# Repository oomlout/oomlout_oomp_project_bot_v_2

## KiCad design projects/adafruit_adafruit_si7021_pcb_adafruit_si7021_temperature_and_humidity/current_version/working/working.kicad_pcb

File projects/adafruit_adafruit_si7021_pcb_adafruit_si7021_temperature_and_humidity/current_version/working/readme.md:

# adafruit_si7021_pcb
 
## summary 
* id: adafruit_adafruit_si7021_pcb_adafruit_si7021_temperature_and_humidity
* user: adafruit
* name: adafruit_si7021_pcb
* board: adafruit_si7021_temperature_and_humidity
* repo: https://github.com/adafruit/Adafruit-Si7021-PCB

* src_file_repo_sch: 
* src_file_repo_sch_link: https://github.com/adafruit/Adafruit-Si7021-PCB/tree/master/
* full details link: https://github.com/oomlout/oomlout_oomp_project_bot_v_2/tree/main/projects/adafruit_adafruit_si7021_pcb_adafruit_si7021_temperature_and_humidity/current_version/working  

## schematic  
  
[schematic (pdf)](working_schematic.pdf) 

## pcb  

[board (pdf)](working.pdf)  

## working_bom
| Id | Designator | Footprint | Quantity | Designation | Supplier and ref |  | None | 
| --- | --- | --- | --- | --- | --- | --- | --- | 
| 1 | Q1,Q2 | SOT23-WIDE | 2 | BSS138 |  |  | [''] | 
| 2 | R2,R3,R1,R4 | 0805-NO | 4 | 10K |  |  | [''] | 
| 3 | U$7,U$6 | MOUNTINGHOLE_2.5_PLATED | 2 | MOUNTINGHOLE2.5 |  |  | [''] | 
| 4 | C2,C3 | 0805-NO | 2 | 10uF |  |  | [''] | 
| 5 | JP1 | 1X05_ROUND_70 | 1 |  |  |  | [''] | 
| 6 | FID1,FID2 | FIDUCIAL_1MM | 2 | FIDUCIAL" |  |  | [''] | 
| 7 | U$1 | ADAFRUIT_2.5MM | 1 |  |  |  | [''] | 
| 8 | C1 | 0805-NO | 1 | 0.1uF |  |  | [''] | 
| 9 | U2 | DFN6_3X3_SI | 1 | Si7021-A20 |  |  | [''] | 
| 10 | U1 | SOT23-5 | 1 | MIC5225-3.3 |  |  | [''] | 
| 11 | U$10 | ADAFRUIT_3.5MM | 1 |  |  |  | [''] | 
| 12 | U$9 | PCBFEAT-REV-040 | 1 |  |  |  | [''] | 

## bom_schematic
| Ref | Qnty | Value | Cmp name | Footprint | Description | Vendor | DNP | 
| --- | --- | --- | --- | --- | --- | --- | --- | 
| C1 | 1 | 0.1uF | CAP_CERAMIC0805-NOOUTLINE | working:0805-NO |  |  |  | 
| C2, C3 | 2 | 10uF | CAP_CERAMIC0805-NOOUTLINE | working:0805-NO |  |  |  | 
| FID1, FID2 | 2 | FIDUCIAL"" | FIDUCIAL{dblquote}{dblquote} | working:FIDUCIAL_1MM |  |  |  | 
| JP1 | 1 | HEADER-1X570MIL | HEADER-1X570MIL | working:1X05_ROUND_70 |  |  |  | 
| Q1, Q2 | 2 | BSS138 | MOSFET-NWIDE | working:SOT23-WIDE |  |  |  | 
| R1, R2, R3, R4 | 4 | 10K | RESISTOR0805_NOOUTLINE | working:0805-NO |  |  |  | 
| U1 | 1 | MIC5225-3.3 | VREG_SOT23-5 | working:SOT23-5 |  |  |  | 
| U2 | 1 | Si7021-A20 | SI7021-A20 | working:DFN6_3X3_SI |  |  |  | 
| U$6, U$7 | 2 | MOUNTINGHOLE2.5 | MOUNTINGHOLE2.5 | working:MOUNTINGHOLE_2.5_PLATED |  |  |  | 

## mounting_holes
| x | y | package | value | ref | size | 
| --- | --- | --- | --- | --- | --- | 
| 10.16 | 0.0 | MOUNTINGHOLE_2.5_PLATED | MOUNTINGHOLE2.5 | U$6 | m3 | 
| 0.0 | 0.0 | MOUNTINGHOLE_2.5_PLATED | MOUNTINGHOLE2.5 | U$7 | m3 |

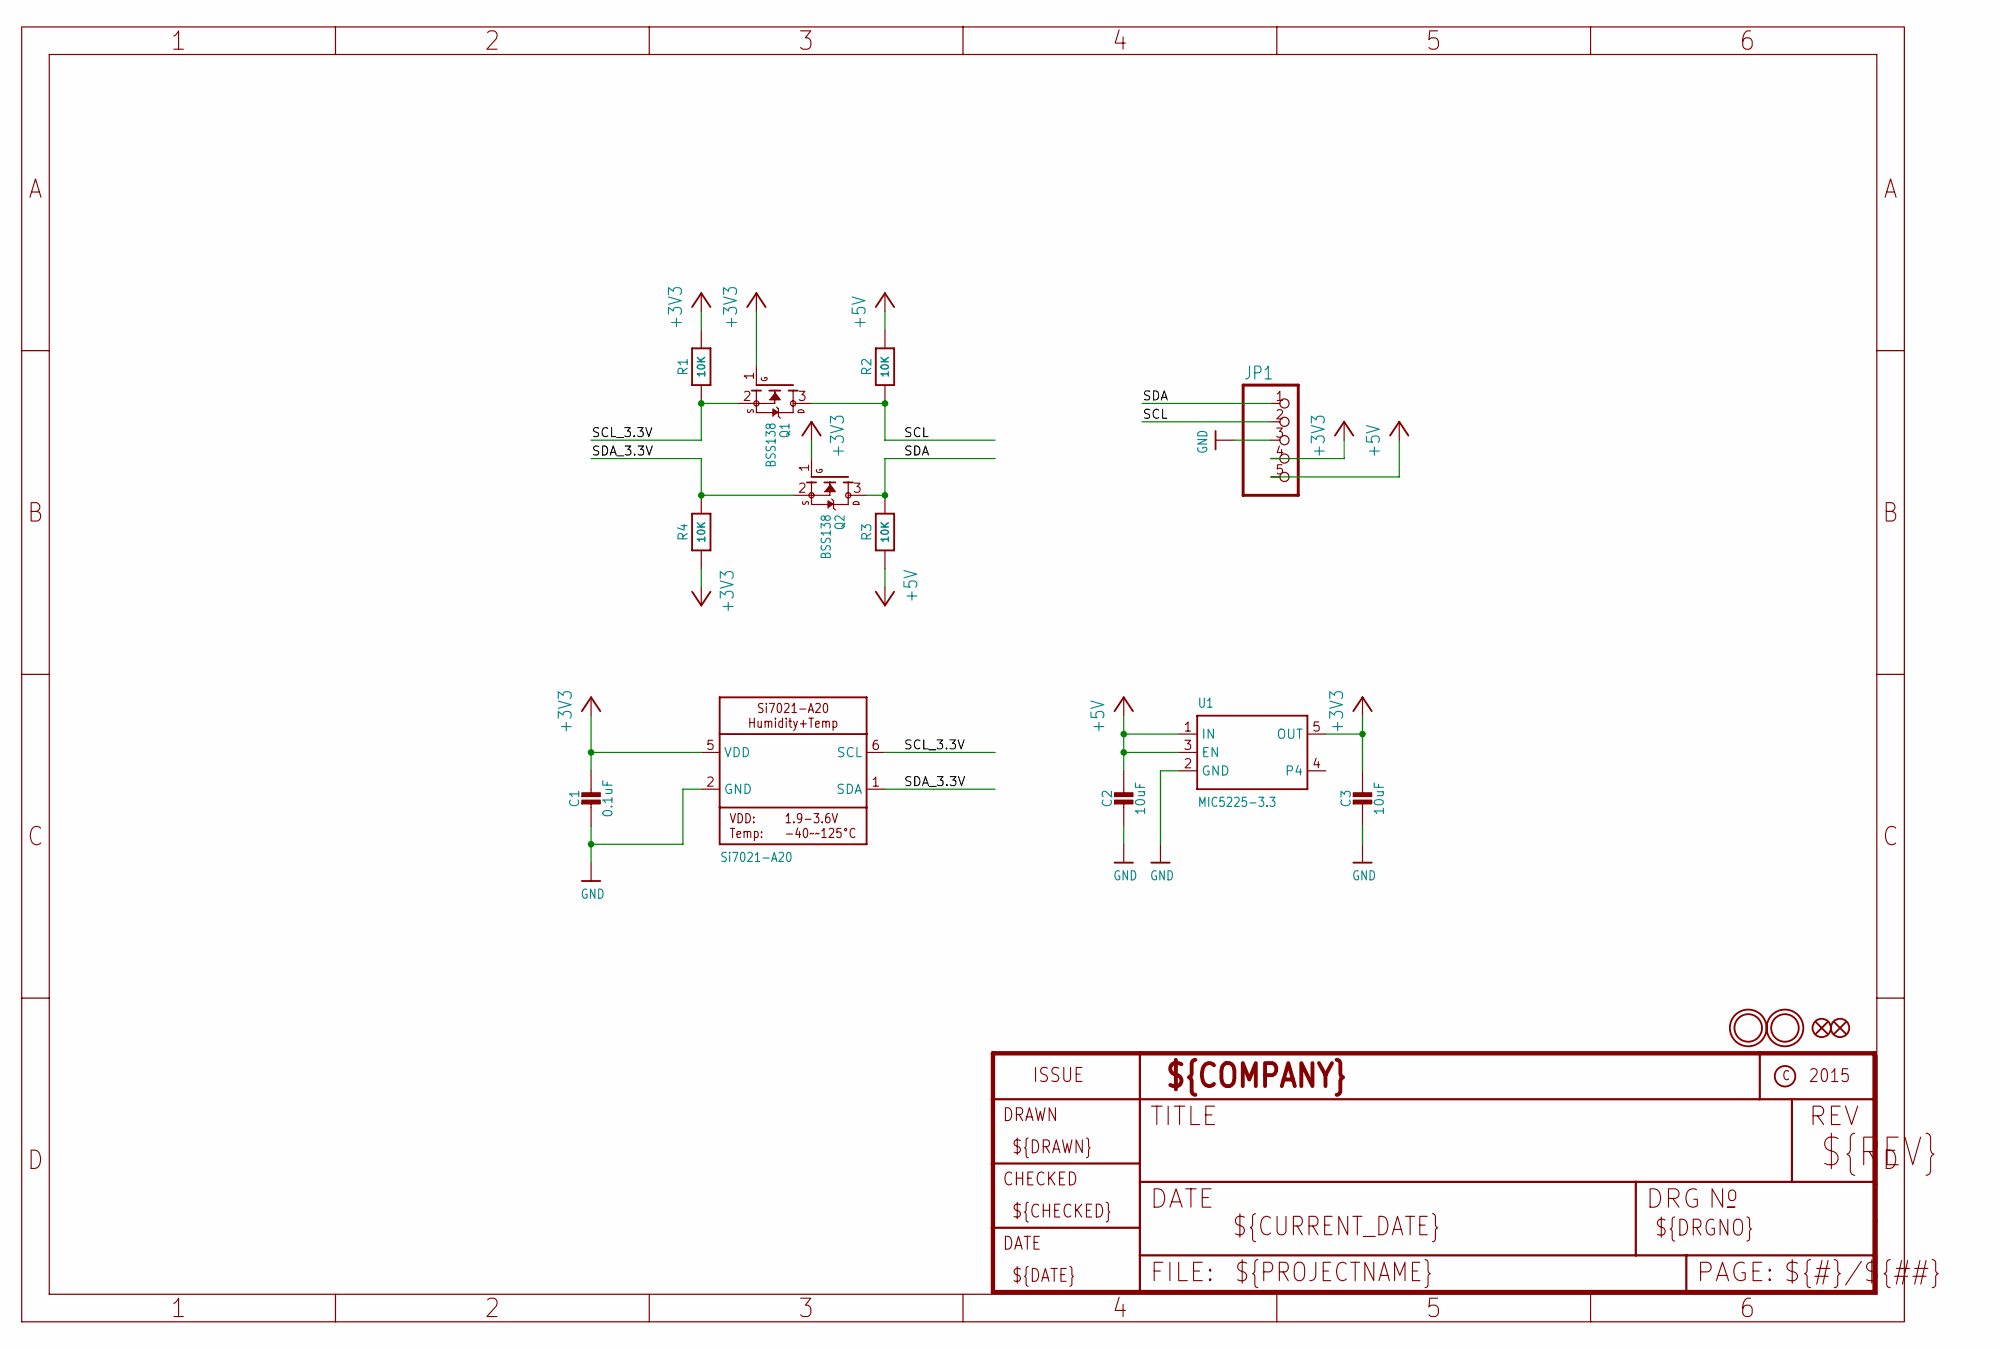
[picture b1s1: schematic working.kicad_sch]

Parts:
C1: 0.1uF; 0805-NO
C2, C3: 10uF; 0805-NO
FID1, FID2: FIDUCIAL""; FIDUCIAL_1MM
JP1: HEADER-1X570MIL; 1X05_ROUND_70
Q1, Q2: BSS138; SOT23-WIDE
R1, R2, R3, R4: 10K; 0805-NO
U1: MIC5225-3.3; SOT23-5
U2: Si7021-A20; DFN6_3X3_SI
U$6, U$7: MOUNTINGHOLE2.5; MOUNTINGHOLE_2.5_PLATED

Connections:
+3V3: C1.1, C3.1, JP1.4, Q1.1 (G), Q2.1 (G), R1.2, R4.1, U1.5 (OUT), U2.5 (VDD)
GND: C1.2, C2.2, C3.2, JP1.3, U1.2 (GND), U2.2 (GND)
SCL: JP1.2, Q1.3 (D), R2.1
SCL_3.3V: Q1.2 (S), R1.1, U2.6 (SCL)
SDA: JP1.1, Q2.3 (D), R3.2
SDA_3.3V: Q2.2 (S), R4.2, U2.1 (SDA)
VIN: C2.1, JP1.5, R2.2, R3.1, U1.1 (IN), U1.3 (EN)

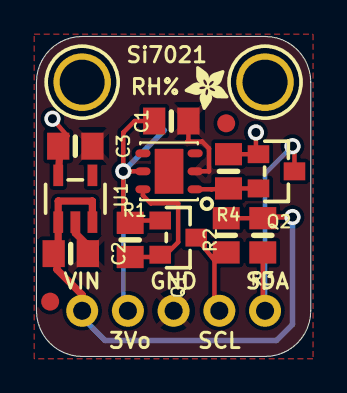
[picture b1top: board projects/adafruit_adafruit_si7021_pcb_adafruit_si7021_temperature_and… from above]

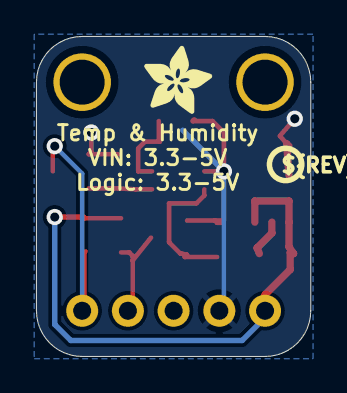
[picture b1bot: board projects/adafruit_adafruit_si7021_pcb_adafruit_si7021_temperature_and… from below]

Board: 2 copper layers, 15.2 x 17.8 mm, 19 parts (2 on the bottom side), 7 nets.

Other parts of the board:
U$1: ADAFRUIT_2.5MM
U$9: PCBFEAT-REV-040
U$10: ADAFRUIT_3.5MM

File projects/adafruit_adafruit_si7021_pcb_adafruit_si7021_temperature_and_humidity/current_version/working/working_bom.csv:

"Id";"Designator";"Footprint";"Quantity";"Designation";"Supplier and ref";
1;"Q1,Q2";"SOT23-WIDE";2;"BSS138";;;
2;"R2,R3,R1,R4";"0805-NO";4;"10K";;;
3;"U$7,U$6";"MOUNTINGHOLE_2.5_PLATED";2;"MOUNTINGHOLE2.5";;;
4;"C2,C3";"0805-NO";2;"10uF";;;
5;"JP1";"1X05_ROUND_70";1;"";;;
6;"FID1,FID2";"FIDUCIAL_1MM";2;"FIDUCIAL""";;;
7;"U$1";"ADAFRUIT_2.5MM";1;"";;;
8;"C1";"0805-NO";1;"0.1uF";;;
9;"U2";"DFN6_3X3_SI";1;"Si7021-A20";;;
10;"U1";"SOT23-5";1;"MIC5225-3.3";;;
11;"U$10";"ADAFRUIT_3.5MM";1;"";;;
12;"U$9";"PCBFEAT-REV-040";1;"";;;

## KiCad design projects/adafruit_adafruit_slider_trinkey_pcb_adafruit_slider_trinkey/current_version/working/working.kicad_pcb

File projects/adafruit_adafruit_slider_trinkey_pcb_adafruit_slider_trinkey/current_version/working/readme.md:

# adafruit_slider_trinkey_pcb
 
## summary 
* id: adafruit_adafruit_slider_trinkey_pcb_adafruit_slider_trinkey
* user: adafruit
* name: adafruit_slider_trinkey_pcb
* board: adafruit_slider_trinkey
* repo: https://github.com/adafruit/Adafruit-Slider-Trinkey-PCB

* src_file_repo_sch: 
* src_file_repo_sch_link: https://github.com/adafruit/Adafruit-Slider-Trinkey-PCB/tree/main/
* full details link: https://github.com/oomlout/oomlout_oomp_project_bot_v_2/tree/main/projects/adafruit_adafruit_slider_trinkey_pcb_adafruit_slider_trinkey/current_version/working  

## schematic  
  
[schematic (pdf)](working_schematic.pdf) 

## pcb  

[board (pdf)](working.pdf)  

## working_bom
| Id | Designator | Footprint | Quantity | Designation | Supplier and ref |  | None | 
| --- | --- | --- | --- | --- | --- | --- | --- | 
| 1 | LED2,LED1 | NEO3535_REVERSE | 2 | WS2812B_SK6812E |  |  | [''] | 
| 2 | POT1 | SLIDE_POT_35MM | 1 | SLIDE_POT_35MM |  |  | [''] | 
| 3 | CN1 | USBA_PCB | 1 | USB A |  |  | [''] | 
| 4 | TOUCH0 | TESTPOINT_ROUND_0.5MM | 1 |  |  |  | [''] | 
| 5 | C3,C8 | 0805-NO | 2 | 10uF |  |  | [''] | 
| 6 | RST0,SWD0 | TP16R | 2 | TPTP16R |  |  | [''] | 
| 7 | U1 | SOT23-5 | 1 | AP2112K-3.3 |  |  | [''] | 
| 8 | FID2,FID1 | FIDUCIAL_1MM | 2 | FIDUCIAL_1MM |  |  | [''] | 
| 9 | C4,C5 | 0603-NO | 2 | 1uF |  |  | [''] | 
| 10 | SWC0 | TP15R | 1 | TPTP15R |  |  | [''] | 
| 11 | IC3 | QFN32_5MM | 1 | ATSAMD21E |  |  | [''] | 
| 12 | U$6 | ADAFRUIT_9MM | 1 |  |  |  | [''] | 
| 13 | U$8 | PCBFEAT-REV-040 | 1 |  |  |  | [''] | 
| 14 | Q2 | BTN_KMR2_4.6X2.8 | 1 | reset |  |  | [''] | 

## bom_schematic
| Ref | Qnty | Value | Cmp name | Footprint | Description | Vendor | DNP | 
| --- | --- | --- | --- | --- | --- | --- | --- | 
| C3, C8 | 2 | 10uF | CAP_CERAMIC0805-NOOUTLINE | working:0805-NO |  |  |  | 
| C4, C5 | 2 | 1uF | CAP_CERAMIC0603_NO | working:0603-NO |  |  |  | 
| CN1 | 1 | USB A | USB_TYPEAPCB | working:USBA_PCB |  |  |  | 
| FID1, FID2 | 2 | FIDUCIAL_1MM | FIDUCIAL_1MM | working:FIDUCIAL_1MM |  |  |  | 
| IC3 | 1 | ATSAMD21E | ATSAMD21E | working:QFN32_5MM |  |  |  | 
| LED1, LED2 | 2 | WS2812B_SK6812E | WS2812B_SK6812E | working:NEO3535_REVERSE |  |  |  | 
| POT1 | 1 | SLIDE_POT_35MM | SLIDE_POT_35MM | working:SLIDE_POT_35MM |  |  |  | 
| Q2 | 1 | reset | SWITCH_TACT_SMT4.6X2.8 | working:BTN_KMR2_4.6X2.8 |  |  |  | 
| RST0 | 1 | TPTP16R | TPTP16R | working:TP16R |  |  |  | 
| SWC0 | 1 | TPTP15R | TPTP15R | working:TP15R |  |  |  | 
| SWD0 | 1 | TPTP16R | TPTP16R | working:TP16R |  |  |  | 
| TOUCH0 | 1 | TESTPOINTROUND0.5MM | TESTPOINTROUND0.5MM | working:TESTPOINT_ROUND_0.5MM |  |  |  | 
| U1 | 1 | AP2112K-3.3 | VREG_SOT23-5 | working:SOT23-5 |  |  |  |

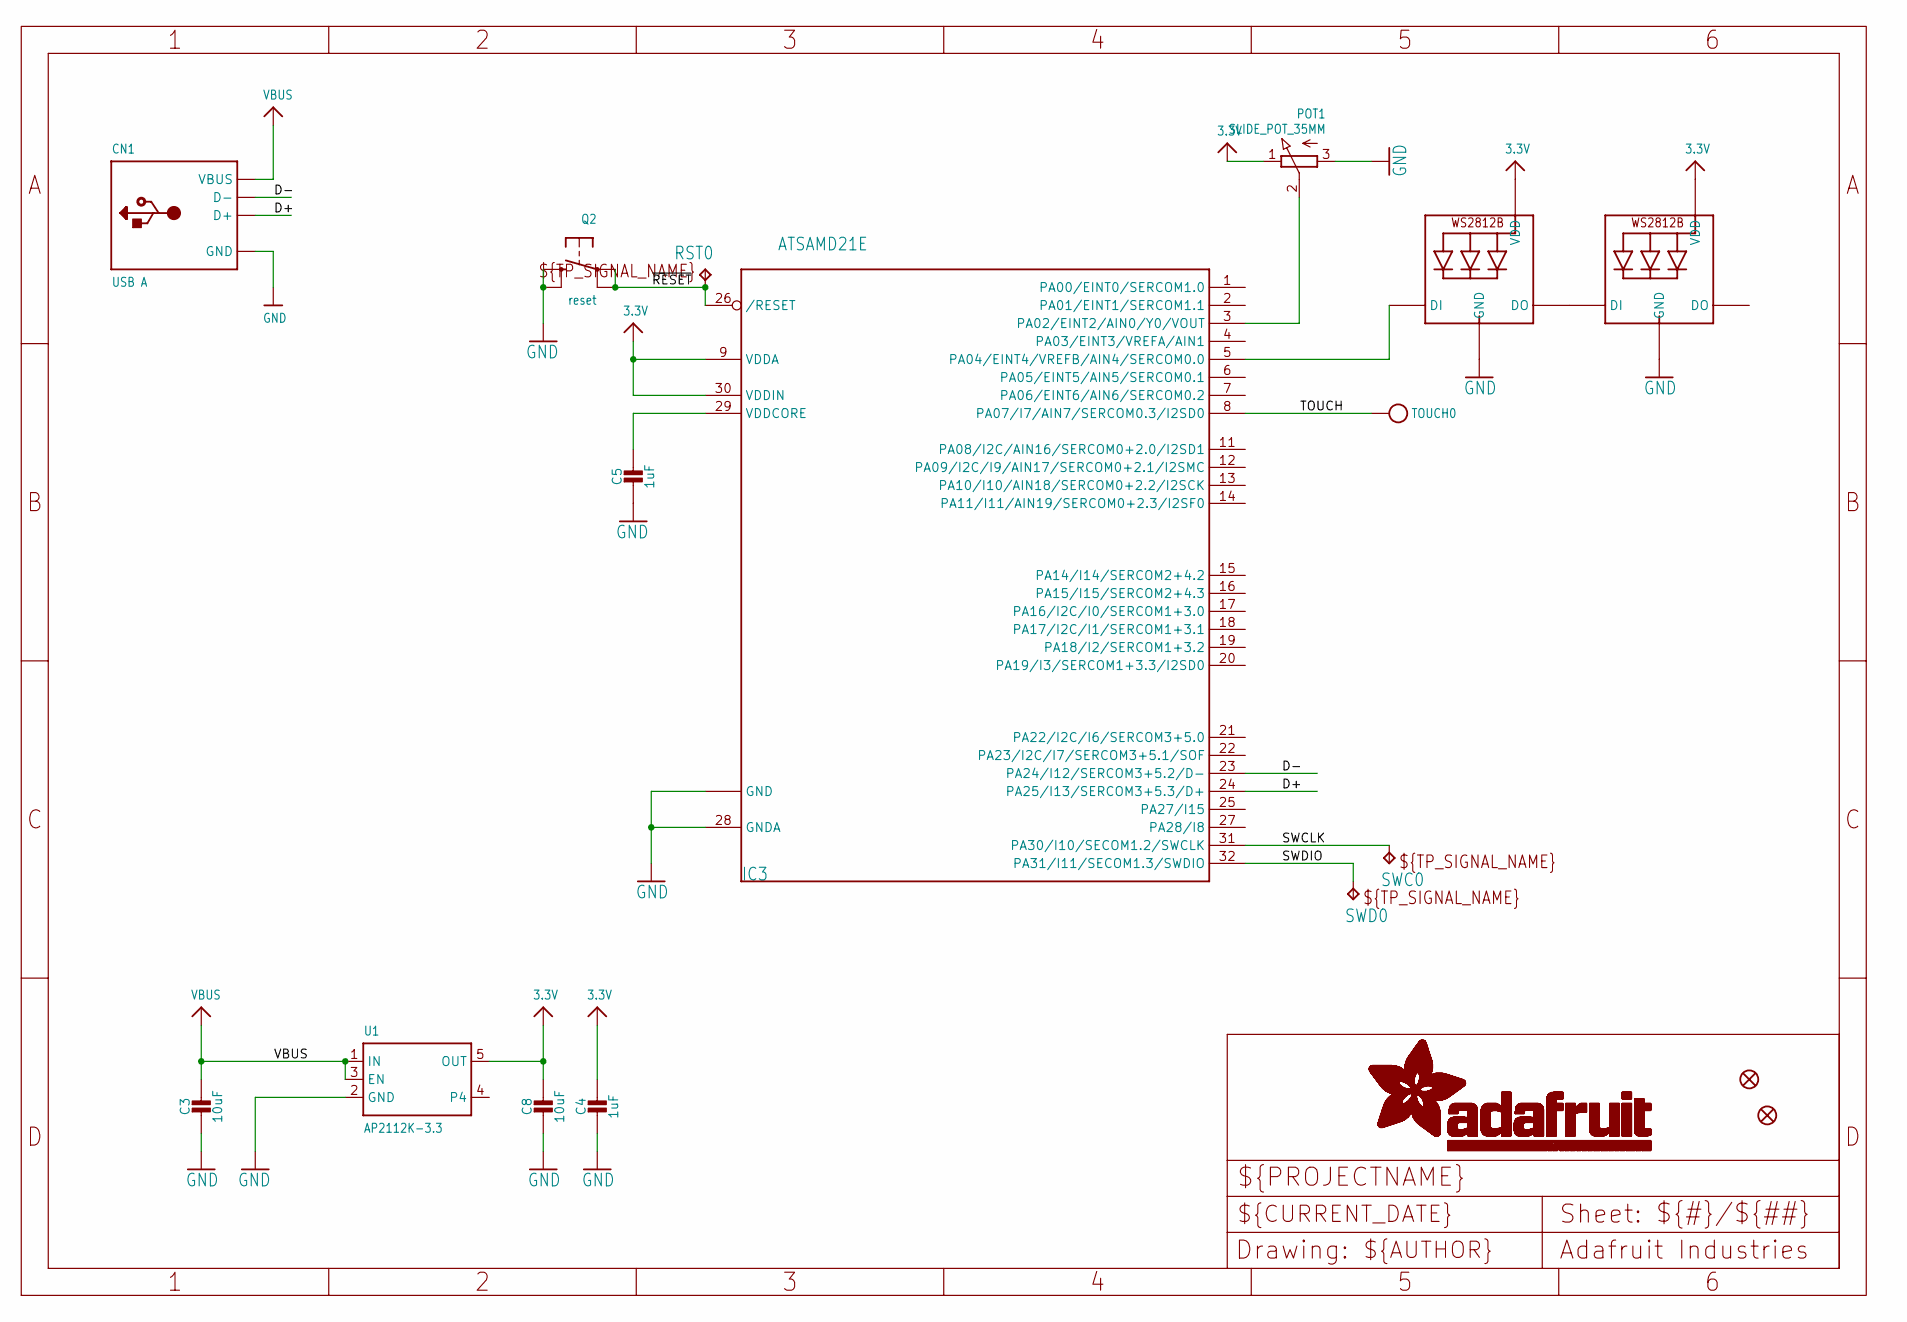
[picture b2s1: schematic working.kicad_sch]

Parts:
C3, C8: 10uF; 0805-NO
C4, C5: 1uF; 0603-NO
CN1: USB A; USBA_PCB
FID1, FID2: FIDUCIAL_1MM
IC3: ATSAMD21E; QFN32_5MM
LED1, LED2: WS2812B_SK6812E; NEO3535_REVERSE
POT1: SLIDE_POT_35MM
Q2: reset; BTN_KMR2_4.6X2.8
RST0: TPTP16R; TP16R
SWC0: TPTP15R; TP15R
SWD0: TPTP16R; TP16R
TOUCH0: TESTPOINTROUND0.5MM; TESTPOINT_ROUND_0.5MM
U1: AP2112K-3.3; SOT23-5

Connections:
3.3V: C4.1, C8.1, IC3.9 (VDDA), IC3.30 (VDDIN), LED1.1-VDD (VDD), LED2.1-VDD (VDD), POT1.1 (E), U1.5 (OUT)
D+: CN1.USB_PLUS (D+), IC3.24 (PA25/I13/SERCOM3+5.3/D+)
D-: CN1.USB_NEG (D-), IC3.23 (PA24/I12/SERCOM3+5.2/D-)
GND: C3.2, C4.2, C5.2, C8.2, CN1.GND, IC3.10 (GND), IC3.28 (GNDA), IC3.33 (GND), LED1.3-GND (GND), LED2.3-GND (GND), POT1.3 (A), Q2.B (S), Q2.B' (S1), U1.2 (GND)
unnamed: IC3.5 (PA04/EINT4/VREFB/AIN4/SERCOM0.0), LED1.4-DIN (DI)
unnamed: LED1.2-DOUT (DO), LED2.4-DIN (DI)
POT: IC3.3 (PA02/EINT2/AIN0/Y0/VOUT), POT1.2 (S)
SWCLK: IC3.31 (PA30/I10/SECOM1.2/SWCLK), SWC0.TP
SWDIO: IC3.32 (PA31/I11/SECOM1.3/SWDIO), SWD0.TP
TOUCH: IC3.8 (PA07/I7/AIN7/SERCOM0.3/I2SD0), TOUCH0.P$1
VBUS: C3.1, CN1.VCC (VBUS), U1.1 (IN), U1.3 (EN)
VDDCORE1: C5.1, IC3.29 (VDDCORE)
~RESET: IC3.26 (/RESET), Q2.A, Q2.A' (P1), RST0.TP

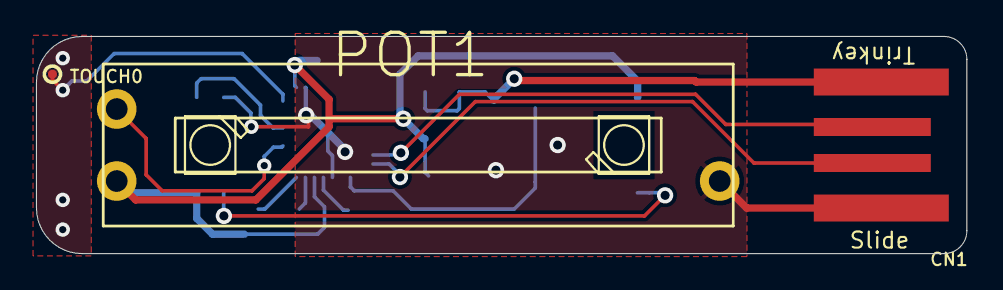
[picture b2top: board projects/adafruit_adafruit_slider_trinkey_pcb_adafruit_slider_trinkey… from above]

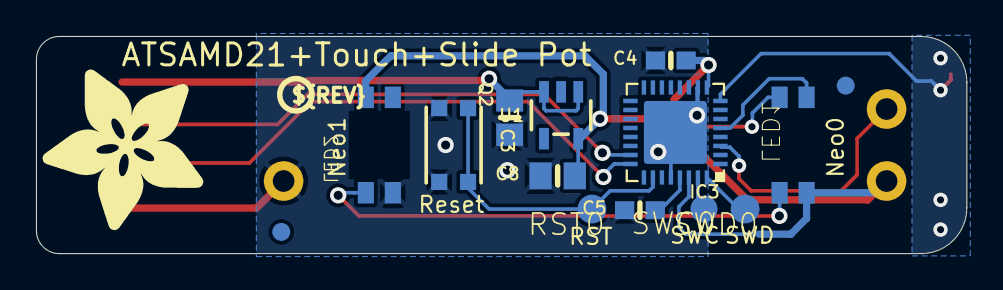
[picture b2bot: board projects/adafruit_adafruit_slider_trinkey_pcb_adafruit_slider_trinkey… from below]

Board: 2 copper layers, 51.7 x 12.1 mm, 19 parts (14 on the bottom side), 13 nets.

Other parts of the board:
U$6: ADAFRUIT_9MM
U$8: PCBFEAT-REV-040

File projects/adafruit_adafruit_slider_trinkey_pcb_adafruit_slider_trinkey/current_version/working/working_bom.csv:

"Id";"Designator";"Footprint";"Quantity";"Designation";"Supplier and ref";
1;"LED2,LED1";"NEO3535_REVERSE";2;"WS2812B_SK6812E";;;
2;"POT1";"SLIDE_POT_35MM";1;"SLIDE_POT_35MM";;;
3;"CN1";"USBA_PCB";1;"USB A";;;
4;"TOUCH0";"TESTPOINT_ROUND_0.5MM";1;"";;;
5;"C3,C8";"0805-NO";2;"10uF";;;
6;"RST0,SWD0";"TP16R";2;"TPTP16R";;;
7;"U1";"SOT23-5";1;"AP2112K-3.3";;;
8;"FID2,FID1";"FIDUCIAL_1MM";2;"FIDUCIAL_1MM";;;
9;"C4,C5";"0603-NO";2;"1uF";;;
10;"SWC0";"TP15R";1;"TPTP15R";;;
11;"IC3";"QFN32_5MM";1;"ATSAMD21E";;;
12;"U$6";"ADAFRUIT_9MM";1;"";;;
13;"U$8";"PCBFEAT-REV-040";1;"";;;
14;"Q2";"BTN_KMR2_4.6X2.8";1;"reset";;;

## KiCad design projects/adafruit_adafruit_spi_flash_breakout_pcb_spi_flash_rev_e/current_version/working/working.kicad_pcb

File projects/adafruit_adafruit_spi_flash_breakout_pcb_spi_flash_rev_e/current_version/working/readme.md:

# adafruit_spi_flash_breakout_pcb
 
## summary 
* id: adafruit_adafruit_spi_flash_breakout_pcb_spi_flash_rev_e
* user: adafruit
* name: adafruit_spi_flash_breakout_pcb
* board: spi_flash_rev_e
* repo: https://github.com/adafruit/Adafruit-SPI-Flash-Breakout-PCB

* src_file_repo_sch: 
* src_file_repo_sch_link: https://github.com/adafruit/Adafruit-SPI-Flash-Breakout-PCB/tree/main/
* full details link: https://github.com/oomlout/oomlout_oomp_project_bot_v_2/tree/main/projects/adafruit_adafruit_spi_flash_breakout_pcb_spi_flash_rev_e/current_version/working  

## schematic  
  
[schematic (pdf)](working_schematic.pdf) 

## pcb  

[board (pdf)](working.pdf)  

## working_bom
| Id | Designator | Footprint | Quantity | Designation | Supplier and ref |  | None | 
| --- | --- | --- | --- | --- | --- | --- | --- | 
| 1 | C3,C4 | 0805-NO | 2 | 10uF |  |  | [''] | 
| 2 | C1 | 0603-NO | 1 | 0.1uF |  |  | [''] | 
| 3 | R1 | 0603-NO | 1 | 10K |  |  | [''] | 
| 4 | U$13 | ADAFRUIT_2.5MM | 1 |  |  |  | [''] | 
| 5 | U1 | SOIC8_208MIL | 1 | Generic SPI Flash |  |  | [''] | 
| 6 | U4 | SOT23-5 | 1 | AP2127K-3.3 |  |  | [''] | 
| 7 | FID3,FID2 | FIDUCIAL_1MM | 2 | FIDUCIAL_1MM |  |  | [''] | 
| 8 | JP2 | 1X07_ROUND_70 | 1 |  |  |  | [''] | 
| 9 | U$16,U$17 | MOUNTINGHOLE_2.5_PLATED | 2 | MOUNTINGHOLE2.5 |  |  | [''] | 
| 10 | U3 | TSSOP16 | 1 | 74HC4050D |  |  | [''] | 
| 11 | U$21 | PCBFEAT-REV-040 | 1 |  |  |  | [''] | 

## bom_schematic
| Ref | Qnty | Value | Cmp name | Footprint | Description | Vendor | DNP | 
| --- | --- | --- | --- | --- | --- | --- | --- | 
| C1 | 1 | 0.1uF | CAP_CERAMIC0603_NO | working:0603-NO |  |  |  | 
| C3, C4 | 2 | 10uF | CAP_CERAMIC0805-NOOUTLINE | working:0805-NO |  |  |  | 
| FID2, FID3 | 2 | FIDUCIAL_1MM | FIDUCIAL_1MM | working:FIDUCIAL_1MM |  |  |  | 
| JP2 | 1 | HEADER-1X770MIL | HEADER-1X770MIL | working:1X07_ROUND_70 |  |  |  | 
| R1 | 1 | 10K | RESISTOR_0603_NOOUT | working:0603-NO |  |  |  | 
| U1 | 1 | Generic SPI Flash | SPIFLASH_8PIN208MIL | working:SOIC8_208MIL |  |  |  | 
| U3 | 1 | 74HC4050D | 74HC4050DTSSOP | working:TSSOP16 |  |  |  | 
| U4 | 1 | AP2127K-3.3 | VREG_SOT23-5 | working:SOT23-5 |  |  |  | 
| U$16, U$17 | 2 | MOUNTINGHOLE2.5 | MOUNTINGHOLE2.5 | working:MOUNTINGHOLE_2.5_PLATED |  |  |  | 

## mounting_holes
| x | y | package | value | ref | size | 
| --- | --- | --- | --- | --- | --- | 
| 0.0 | 0.0 | MOUNTINGHOLE_2.5_PLATED | MOUNTINGHOLE2.5 | U$16 | m3 | 
| 15.24 | 0.0 | MOUNTINGHOLE_2.5_PLATED | MOUNTINGHOLE2.5 | U$17 | m3 |

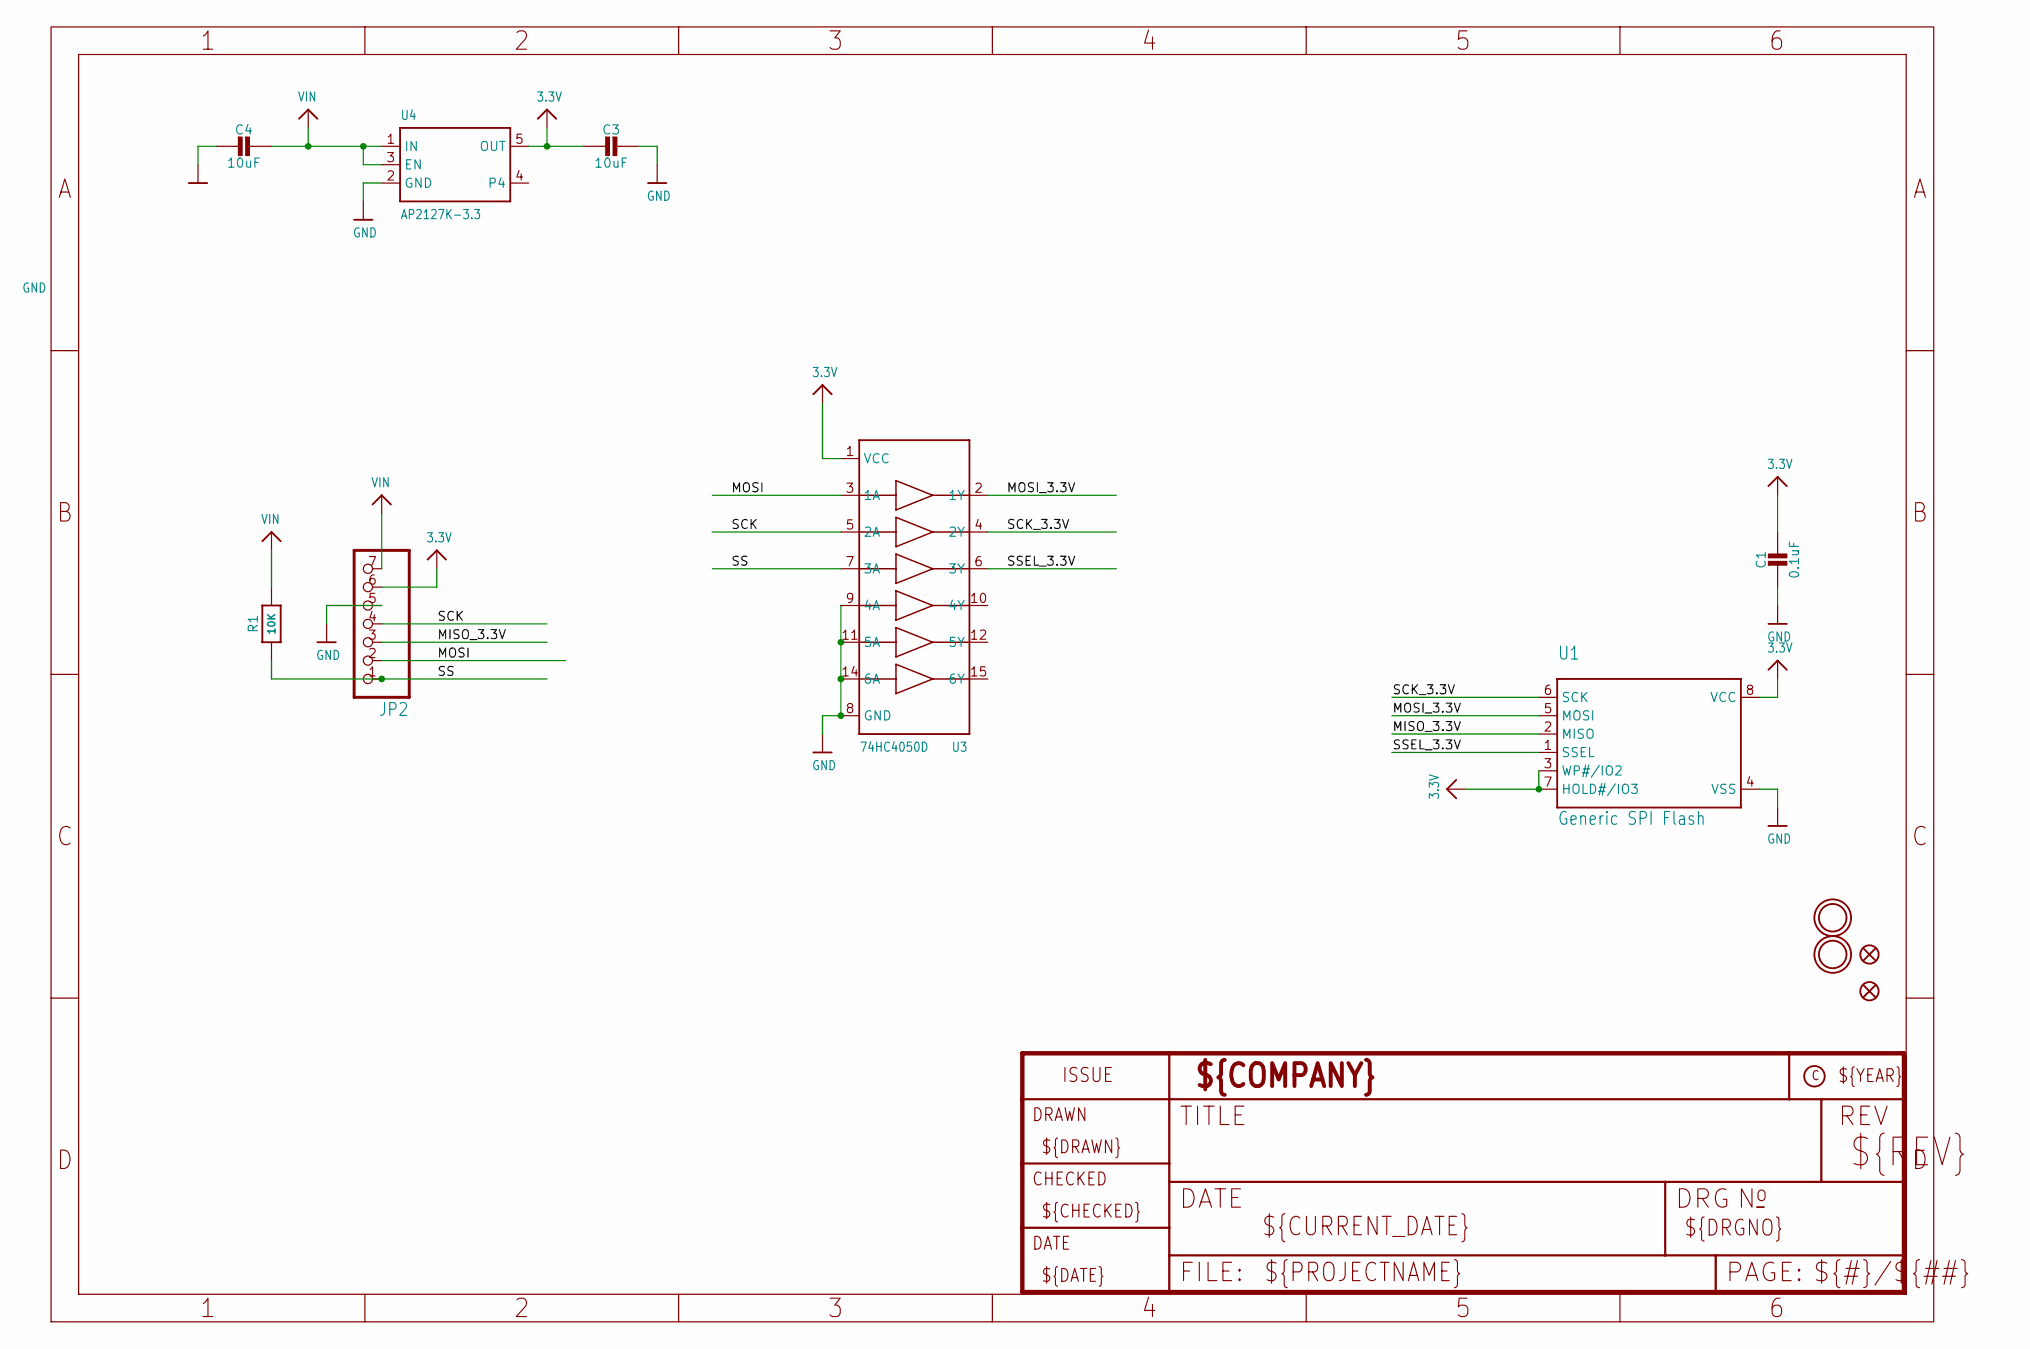
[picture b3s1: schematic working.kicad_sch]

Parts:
C1: 0.1uF; 0603-NO
C3, C4: 10uF; 0805-NO
FID2, FID3: FIDUCIAL_1MM
JP2: HEADER-1X770MIL; 1X07_ROUND_70
R1: 10K; 0603-NO
U1: Generic SPI Flash; SOIC8_208MIL
U3: 74HC4050D; TSSOP16
U4: AP2127K-3.3; SOT23-5
U$16, U$17: MOUNTINGHOLE2.5; MOUNTINGHOLE_2.5_PLATED

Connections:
3.3V: C1.1, C3.2, JP2.6, U1.3 (WP#/IO2), U1.7 (HOLD#/IO3), U1.8 (VCC), U3.1 (VCC), U4.5 (OUT)
GND: C1.2, C3.1, C4.2, JP2.5, U1.4 (VSS), U3.8 (GND), U3.9 (4A), U3.11 (5A), U3.14 (6A), U4.2 (GND)
MISO_3.3V: JP2.3, U1.2 (MISO)
MOSI: JP2.2, U3.3 (1A)
MOSI_3.3V: U1.5 (MOSI), U3.2 (1Y)
SCK: JP2.4, U3.5 (2A)
SCK_3.3V: U1.6 (SCK), U3.4 (2Y)
SS: JP2.1, R1.1, U3.7 (3A)
SSEL_3.3V: U1.1 (SSEL), U3.6 (3Y)
VIN: C4.1, JP2.7, R1.2, U4.1 (IN), U4.3 (EN)

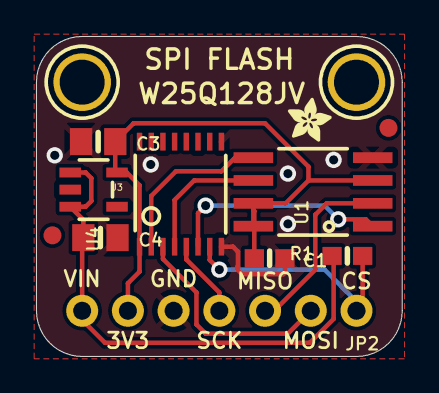
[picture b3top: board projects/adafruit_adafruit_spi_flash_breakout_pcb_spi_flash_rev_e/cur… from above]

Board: 2 copper layers, 20.3 x 17.8 mm, 14 parts (1 on the bottom side), 10 nets.

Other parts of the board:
U$13: ADAFRUIT_2.5MM
U$21: PCBFEAT-REV-040

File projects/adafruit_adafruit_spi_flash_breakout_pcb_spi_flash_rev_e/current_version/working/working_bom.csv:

"Id";"Designator";"Footprint";"Quantity";"Designation";"Supplier and ref";
1;"C3,C4";"0805-NO";2;"10uF";;;
2;"C1";"0603-NO";1;"0.1uF";;;
3;"R1";"0603-NO";1;"10K";;;
4;"U$13";"ADAFRUIT_2.5MM";1;"";;;
5;"U1";"SOIC8_208MIL";1;"Generic SPI Flash";;;
6;"U4";"SOT23-5";1;"AP2127K-3.3";;;
7;"FID3,FID2";"FIDUCIAL_1MM";2;"FIDUCIAL_1MM";;;
8;"JP2";"1X07_ROUND_70";1;"";;;
9;"U$16,U$17";"MOUNTINGHOLE_2.5_PLATED";2;"MOUNTINGHOLE2.5";;;
10;"U3";"TSSOP16";1;"74HC4050D";;;
11;"U$21";"PCBFEAT-REV-040";1;"";;;

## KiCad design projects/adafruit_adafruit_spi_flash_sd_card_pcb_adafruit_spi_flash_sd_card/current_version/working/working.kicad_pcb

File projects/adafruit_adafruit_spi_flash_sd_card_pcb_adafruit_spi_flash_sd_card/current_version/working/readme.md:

# adafruit_spi_flash_sd_card_pcb
 
## summary 
* id: adafruit_adafruit_spi_flash_sd_card_pcb_adafruit_spi_flash_sd_card
* user: adafruit
* name: adafruit_spi_flash_sd_card_pcb
* board: adafruit_spi_flash_sd_card
* repo: https://github.com/adafruit/Adafruit-SPI-Flash-SD-Card-PCB

* src_file_repo_sch: 
* src_file_repo_sch_link: https://github.com/adafruit/Adafruit-SPI-Flash-SD-Card-PCB/tree/main/
* full details link: https://github.com/oomlout/oomlout_oomp_project_bot_v_2/tree/main/projects/adafruit_adafruit_spi_flash_sd_card_pcb_adafruit_spi_flash_sd_card/current_version/working  

## schematic  
  
[schematic (pdf)](working_schematic.pdf) 

## pcb  

[board (pdf)](working.pdf)  

## working_bom
| Id | Designator | Footprint | Quantity | Designation | Supplier and ref |  | None | 
| --- | --- | --- | --- | --- | --- | --- | --- | 
| 1 | C4,C3 | 0805-NO | 2 | 10uF |  |  | [''] | 
| 2 | U5 | LGA8_8X6 | 1 | XTSD |  |  | [''] | 
| 3 | FID2,FID3 | FIDUCIAL_1MM | 2 | FIDUCIAL_1MM |  |  | [''] | 
| 4 | C1 | 0603-NO | 1 | 0.1uF |  |  | [''] | 
| 5 | U$19 | ADAFRUIT_3.5MM | 1 |  |  |  | [''] | 
| 6 | JP2 | 1X07_ROUND_70 | 1 |  |  |  | [''] | 
| 7 | U$17,U$16 | MOUNTINGHOLE_2.5_PLATED | 2 | MOUNTINGHOLE2.5 |  |  | [''] | 
| 8 | U4 | SOT23-5 | 1 | AP2112K-3.3 |  |  | [''] | 
| 9 | U3 | TSSOP16 | 1 | 74HC4050D |  |  | [''] | 
| 10 | R1 | 0603-NO | 1 | 10K |  |  | [''] | 
| 11 | U$21 | PCBFEAT-REV-040 | 1 |  |  |  | [''] | 

## bom_schematic
| Ref | Qnty | Value | Cmp name | Footprint | Description | Vendor | DNP | 
| --- | --- | --- | --- | --- | --- | --- | --- | 
| C1 | 1 | 0.1uF | CAP_CERAMIC0603_NO | working:0603-NO |  |  |  | 
| C3, C4 | 2 | 10uF | CAP_CERAMIC0805-NOOUTLINE | working:0805-NO |  |  |  | 
| FID2, FID3 | 2 | FIDUCIAL_1MM | FIDUCIAL_1MM | working:FIDUCIAL_1MM |  |  |  | 
| JP2 | 1 | HEADER-1X770MIL | HEADER-1X770MIL | working:1X07_ROUND_70 |  |  |  | 
| R1 | 1 | 10K | RESISTOR_0603_NOOUT | working:0603-NO |  |  |  | 
| U3 | 1 | 74HC4050D | 74HC4050DTSSOP | working:TSSOP16 |  |  |  | 
| U4 | 1 | AP2112K-3.3 | VREG_SOT23-5 | working:SOT23-5 |  |  |  | 
| U5 | 1 | XTSD | SMT_SDCARD_8PIN | working:LGA8_8X6 |  |  |  | 
| U$16, U$17 | 2 | MOUNTINGHOLE2.5 | MOUNTINGHOLE2.5 | working:MOUNTINGHOLE_2.5_PLATED |  |  |  | 

## mounting_holes
| x | y | package | value | ref | size | 
| --- | --- | --- | --- | --- | --- | 
| 0.0 | 0.0 | MOUNTINGHOLE_2.5_PLATED | MOUNTINGHOLE2.5 | U$16 | m3 | 
| 16.51 | 0.0 | MOUNTINGHOLE_2.5_PLATED | MOUNTINGHOLE2.5 | U$17 | m3 |

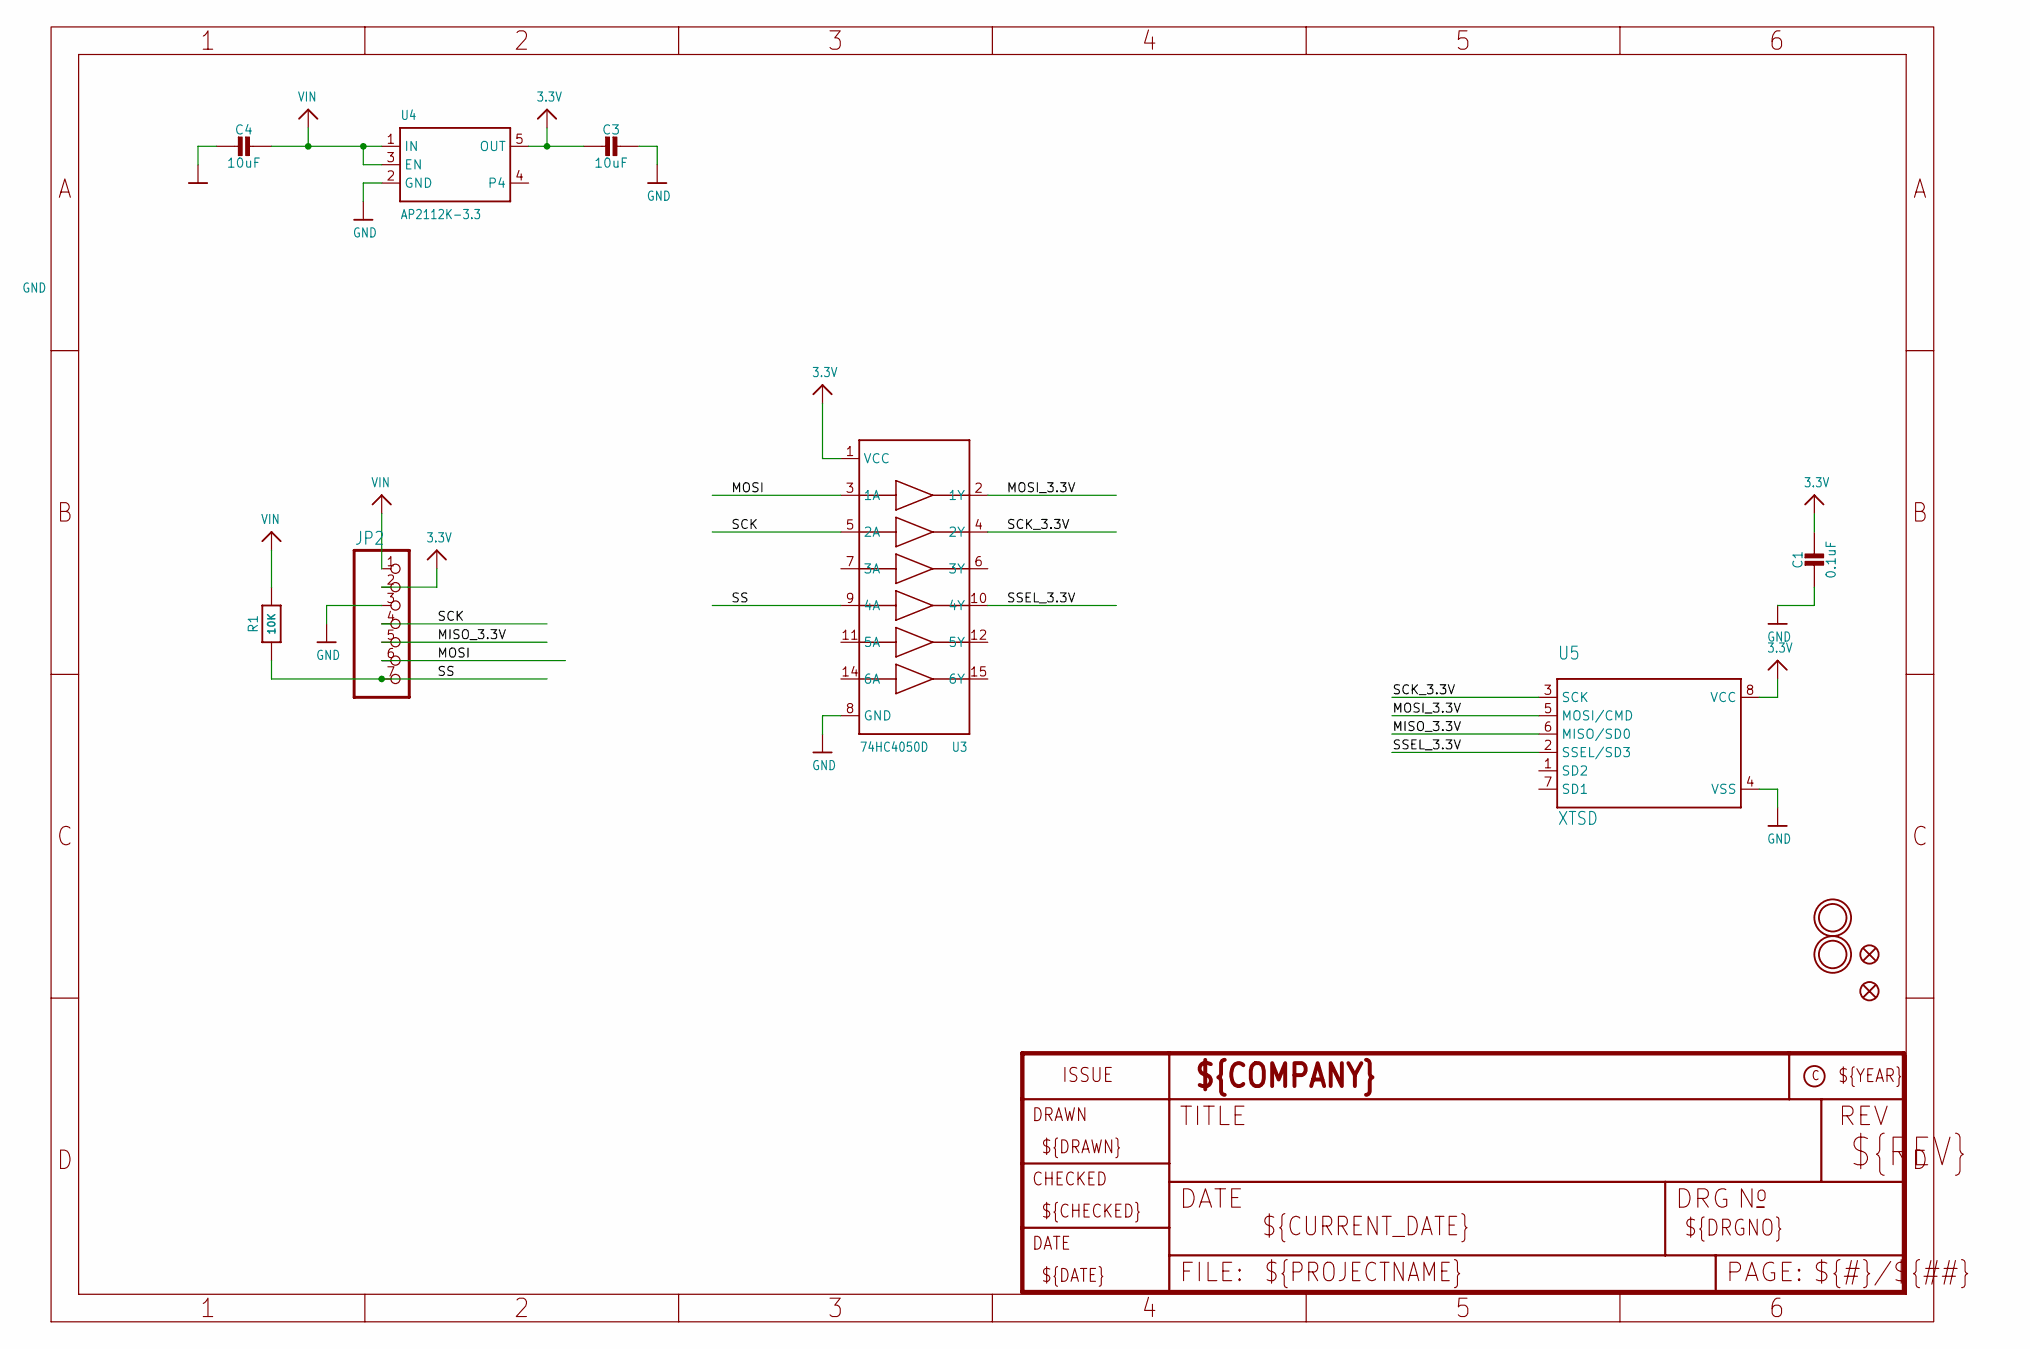
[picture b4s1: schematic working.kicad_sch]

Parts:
C1: 0.1uF; 0603-NO
C3, C4: 10uF; 0805-NO
FID2, FID3: FIDUCIAL_1MM
JP2: HEADER-1X770MIL; 1X07_ROUND_70
R1: 10K; 0603-NO
U3: 74HC4050D; TSSOP16
U4: AP2112K-3.3; SOT23-5
U5: XTSD; LGA8_8X6
U$16, U$17: MOUNTINGHOLE2.5; MOUNTINGHOLE_2.5_PLATED

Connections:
3.3V: C1.1, C3.2, JP2.2, U3.1 (VCC), U4.5 (OUT), U5.8 (VCC)
GND: C1.2, C3.1, C4.2, JP2.3, U3.8 (GND), U4.2 (GND), U5.4 (VSS)
MISO_3.3V: JP2.5, U5.6 (MISO/SD0)
MOSI: JP2.6, U3.3 (1A)
MOSI_3.3V: U3.2 (1Y), U5.5 (MOSI/CMD)
SCK: JP2.4, U3.5 (2A)
SCK_3.3V: U3.4 (2Y), U5.3 (SCK)
SS: JP2.7, R1.1, U3.9 (4A)
SSEL_3.3V: U3.10 (4Y), U5.2 (SSEL/SD3)
VIN: C4.1, JP2.1, R1.2, U4.1 (IN), U4.3 (EN)

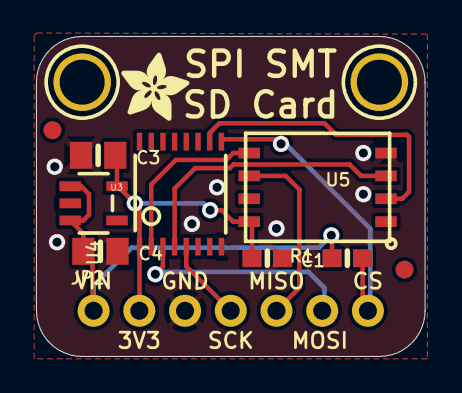
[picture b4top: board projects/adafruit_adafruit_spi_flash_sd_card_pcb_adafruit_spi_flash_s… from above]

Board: 2 copper layers, 21.6 x 17.8 mm, 14 parts (1 on the bottom side), 10 nets.

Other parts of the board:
U$19: ADAFRUIT_3.5MM
U$21: PCBFEAT-REV-040

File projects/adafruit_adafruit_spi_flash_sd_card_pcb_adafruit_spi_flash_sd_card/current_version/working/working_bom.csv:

"Id";"Designator";"Footprint";"Quantity";"Designation";"Supplier and ref";
1;"C4,C3";"0805-NO";2;"10uF";;;
2;"U5";"LGA8_8X6";1;"XTSD";;;
3;"FID2,FID3";"FIDUCIAL_1MM";2;"FIDUCIAL_1MM";;;
4;"C1";"0603-NO";1;"0.1uF";;;
5;"U$19";"ADAFRUIT_3.5MM";1;"";;;
6;"JP2";"1X07_ROUND_70";1;"";;;
7;"U$17,U$16";"MOUNTINGHOLE_2.5_PLATED";2;"MOUNTINGHOLE2.5";;;
8;"U4";"SOT23-5";1;"AP2112K-3.3";;;
9;"U3";"TSSOP16";1;"74HC4050D";;;
10;"R1";"0603-NO";1;"10K";;;
11;"U$21";"PCBFEAT-REV-040";1;"";;;
